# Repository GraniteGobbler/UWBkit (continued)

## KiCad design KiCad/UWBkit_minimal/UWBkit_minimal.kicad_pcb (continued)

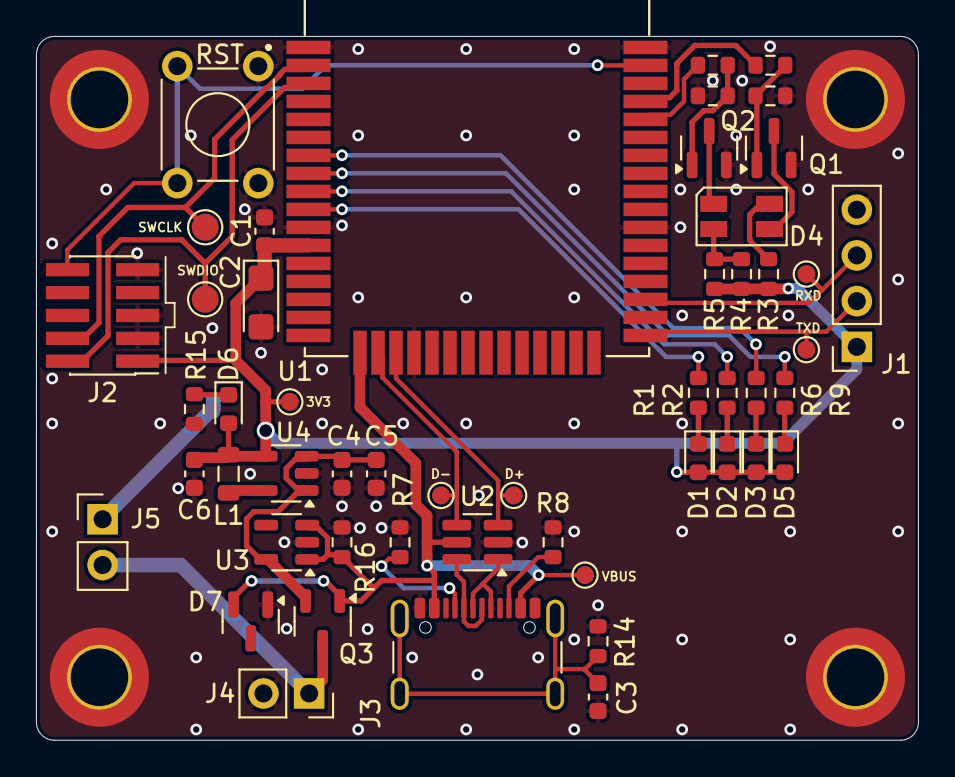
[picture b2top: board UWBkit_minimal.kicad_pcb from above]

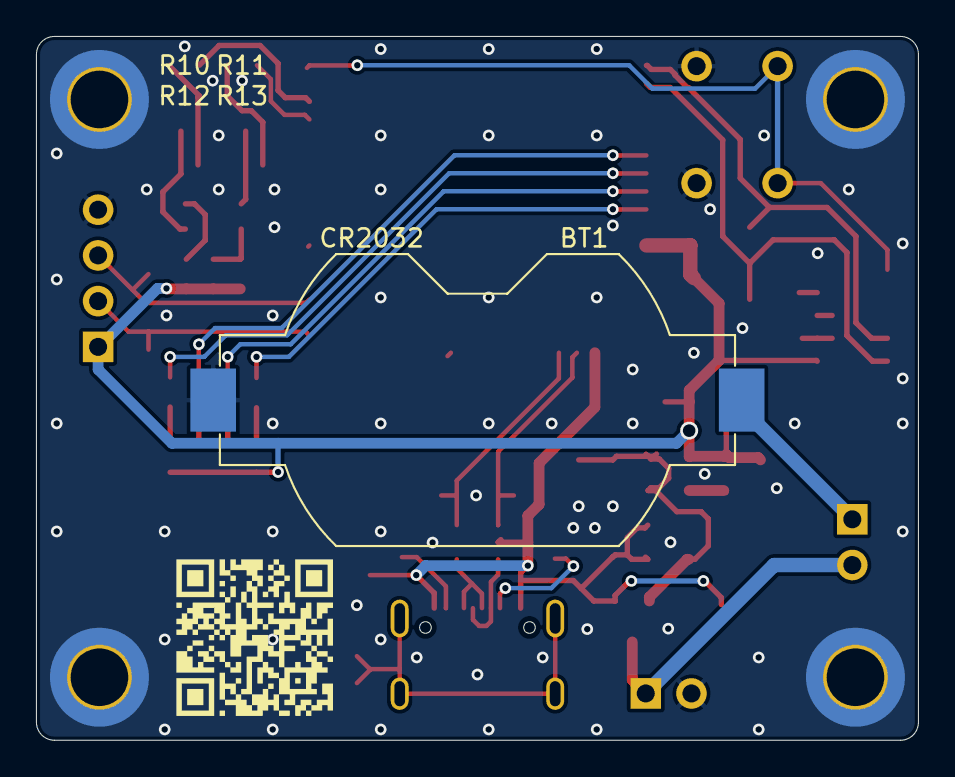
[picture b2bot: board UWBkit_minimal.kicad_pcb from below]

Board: 2 copper layers, 49.0 x 39.1 mm, 57 parts (2 on the bottom side), 36 nets.

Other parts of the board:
QR*****: Git_QR

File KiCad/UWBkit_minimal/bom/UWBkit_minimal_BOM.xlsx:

Reference | Qty | Value | Footprint |  | Mouser link
BT1 | 1 | CR2032 | Battery:BatteryHolder_Keystone_1058_1x2032 | https://cz.mouser.com/ProductDetail/Keystone-Electronics/105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 | https://cz.mouser.com/ProductDetail/Keystone-Electronics/105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
C1,C3,C4 | 3 | 100n | Capacitor_SMD:C_0603_1608Metric | https://cz.mouser.com/ProductDetail/YAGEO/CC0603JRX7R9BB104?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 | https://cz.mouser.com/ProductDetail/YAGEO/CC0603JRX7R9BB104?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
C2 | 1 | 10u | Capacitor_Tantalum_SMD:CP_EIA-3216-18_Kemet-A | https://cz.mouser.com/ProductDetail/KEMET/T491A106K010AT7280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 | https://cz.mouser.com/ProductDetail/KEMET/T491A106K010AT7280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
C5,C6 | 2 | 10u | Capacitor_SMD:C_0603_1608Metric | https://cz.mouser.com/ProductDetail/Murata-Electronics/GRM18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 | https://cz.mouser.com/ProductDetail/Murata-Electronics/GRM18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
D1 | 1 | G | LED_SMD:LED_0603_1608Metric | https://cz.mouser.com/ProductDetail/Wurth-Elektronik/150060G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 | https://cz.mouser.com/ProductDetail/Wurth-Elektronik/150060G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
D2 | 1 | B | LED_SMD:LED_0603_1608Metric | https://cz.mouser.com/ProductDetail/Wurth-Elektronik/150060B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 | https://cz.mouser.com/ProductDetail/Wurth-Elektronik/150060B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
D3,D5,D6 | 3 | R | LED_SMD:LED_0603_1608Metric | https://cz.mouser.com/ProductDetail/Wurth-Elektronik/150060R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 | https://cz.mouser.com/ProductDetail/Wurth-Elektronik/150060R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
D4 | 1 | LSG T676-P7R-1-0+N7P9-24 | LED_Dual:LED_Dual_OSRAM-PLCC4_3.2x2.8mm | https://cz.mouser.com/ProductDetail/ams-OSRAM/LSG-T676-P7R-1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 | https://cz.mouser.com/ProductDetail/ams-OSRAM/LSG-T676-P7R-1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
D7 | 1 | PESD5V2S2UT | Package_TO_SOT_SMD:SOT-23 | https://cz.mouser.com/ProductDetail/Nexperia/PESD5V2S2UT-QR?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 | https://cz.mouser.com/ProductDetail/Nexperia/PESD5V2S2UT-QR?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
J1 | 1 | Conn_UART | Connector_PinSocket_2.54mm:PinSocket_1x04_P2.54mm_Vertical | https://cz.mouser.com/ProductDetail/Samtec/SSQ-104-01-G-S?qs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 | https://cz.mouser.com/ProductDetail/Samtec/SSQ-104-01-G-S?qs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
J2 | 1 | Conn_SWD | Connector_PinHeader_1.27mm:PinHeader_2x05_P1.27mm_Vertical_SMD | https://cz.mouser.com/ProductDetail/Samtec/SHF-105-01-L-D-SM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 | https://cz.mouser.com/ProductDetail/Samtec/SHF-105-01-L-D-SM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
J3 | 1 | USB_C_Receptacle_USB2.0_14P | Connector_USB:USB_C_Receptacle_GCT_USB4105-xx-A_16P_TopMnt_Horizontal | https://cz.mouser.com/ProductDetail/GCT/USB4105-GF-A?qs=KUoI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 | https://cz.mouser.com/ProductDetail/GCT/USB4105-GF-A?qs=KUoI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
J4 | 1 | Conn_BATT | Connector_PinSocket_2.54mm:PinSocket_1x02_P2.54mm_Vertical | https://cz.mouser.com/ProductDetail/Amphenol-FCI/76308-102LF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 | https://cz.mouser.com/ProductDetail/Amphenol-FCI/76308-102LF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
J5 | 1 | Jumper_Cell_NO | Connector_PinHeader_2.54mm:PinHeader_1x02_P2.54mm_Vertical | https://cz.mouser.com/ProductDetail/Amphenol-FCI/10129378-91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 | https://cz.mouser.com/ProductDetail/Amphenol-FCI/10129378-91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
L1 | 1 | 2.2u | Inductor_SMD:L_0805_2012Metric | https://cz.mouser.com/ProductDetail/TDK/MLZ2012M2R2HT000?qs=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 | https://cz.mouser.com/ProductDetail/TDK/MLZ2012M2R2HT000?qs=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
Q1,Q2 | 2 | BSS138 | Package_TO_SOT_SMD:SOT-23 | https://cz.mouser.com/ProductDetail/onsemi-Fairchild/BSS138?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 | https://cz.mouser.com/ProductDetail/onsemi-Fairchild/BSS138?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
Q3 | 1 | BSS84 | Package_TO_SOT_SMD:SOT-23-3 | https://cz.mouser.com/ProductDetail/onsemi-Fairchild/BSS84?q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 | https://cz.mouser.com/ProductDetail/onsemi-Fairchild/BSS84?q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
R1 | 1 | 200R | Resistor_SMD:R_0603_1608Metric | https://cz.mouser.com/ProductDetail/YAGEO/RT0603DRD07200RL?q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 | https://cz.mouser.com/ProductDetail/YAGEO/RT0603DRD07200RL?q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
R2 | 1 | 30R | Resistor_SMD:R_0603_1608Metric | https://cz.mouser.com/ProductDetail/YAGEO/RT0603DRE0730RL?qs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 | https://cz.mouser.com/ProductDetail/YAGEO/RT0603DRE0730RL?qs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
R3 | 1 | 150R | Resistor_SMD:R_0603_1608Metric | https://cz.mouser.com/ProductDetail/YAGEO/AC0603FR-10150RL?q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 | https://cz.mouser.com/ProductDetail/YAGEO/AC0603FR-10150RL?q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
R4 | 1 | 330R | Resistor_SMD:R_0603_1608Metric | https://cz.mouser.com/ProductDetail/YAGEO/RE0603FRE07330RL?q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 | https://cz.mouser.com/ProductDetail/YAGEO/RE0603FRE07330RL?q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
R5 | 1 | 220R | Resistor_SMD:R_0603_1608Metric | https://cz.mouser.com/ProductDetail/Vishay/CRCW0603220RFKEC?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 | https://cz.mouser.com/ProductDetail/Vishay/CRCW0603220RFKEC?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
R6,R9,R15 | 3 | 300R | Resistor_SMD:R_0603_1608Metric | https://cz.mouser.com/ProductDetail/Panasonic/ERA-3AEB301V?q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 | https://cz.mouser.com/ProductDetail/Panasonic/ERA-3AEB301V?q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
R7,R8 | 2 | 5k1 | Resistor_SMD:R_0603_1608Metric | https://cz.mouser.com/ProductDetail/Vishay/CRCW06035K10FKEBC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 | https://cz.mouser.com/ProductDetail/Vishay/CRCW06035K10FKEBC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
R10,R11 | 2 | 1k | Resistor_SMD:R_0603_1608Metric | https://cz.mouser.com/ProductDetail/Vishay-Draloric/RCA06031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 | https://cz.mouser.com/ProductDetail/Vishay-Draloric/RCA06031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
R12,R13,R16 | 3 | 100k | Resistor_SMD:R_0603_1608Metric | https://cz.mouser.com/ProductDetail/YAGEO/RT0603BRD07100KL?q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 | https://cz.mouser.com/ProductDetail/YAGEO/RT0603BRD07100KL?q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
R14 | 1 | 10k | Resistor_SMD:R_0603_1608Metric | https://cz.mouser.com/ProductDetail/YAGEO/RC0603FR-7W10KL?qs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 | https://cz.mouser.com/ProductDetail/YAGEO/RC0603FR-7W10KL?qs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
SW1 | 1 | SW_Push | Button_Switch_THT:SW_TH_Tactile_Omron_B3F-106x | https://cz.mouser.com/ProductDetail/Omron-Electronics/B3F-10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 | https://cz.mouser.com/ProductDetail/Omron-Electronics/B3F-10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
U2 | 1 | IP4234CZ6 | Package_TO_SOT_SMD:SC-74-6_1.55x2.9mm_P0.95mm | https://cz.mouser.com/ProductDetail/Nexperia/IP4234CZ6125?qs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 | https://cz.mouser.com/ProductDetail/Nexperia/IP4234CZ6125?qs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
U3 | 1 | MAX40203AUK+T | Package_TO_SOT_SMD:SOT-23-5 | https://cz.mouser.com/ProductDetail/Analog-Devices-Maxim-Int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 | https://cz.mouser.com/ProductDetail/Analog-Devices-Maxim-Int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
U4 | 1 | XC9285B33CMR-G | Package_TO_SOT_SMD:SOT-23-5 | https://cz.mouser.com/ProductDetail/Torex-Semiconductor/XC92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 | https://cz.mouser.com/ProductDetail/Torex-Semiconductor/XC92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

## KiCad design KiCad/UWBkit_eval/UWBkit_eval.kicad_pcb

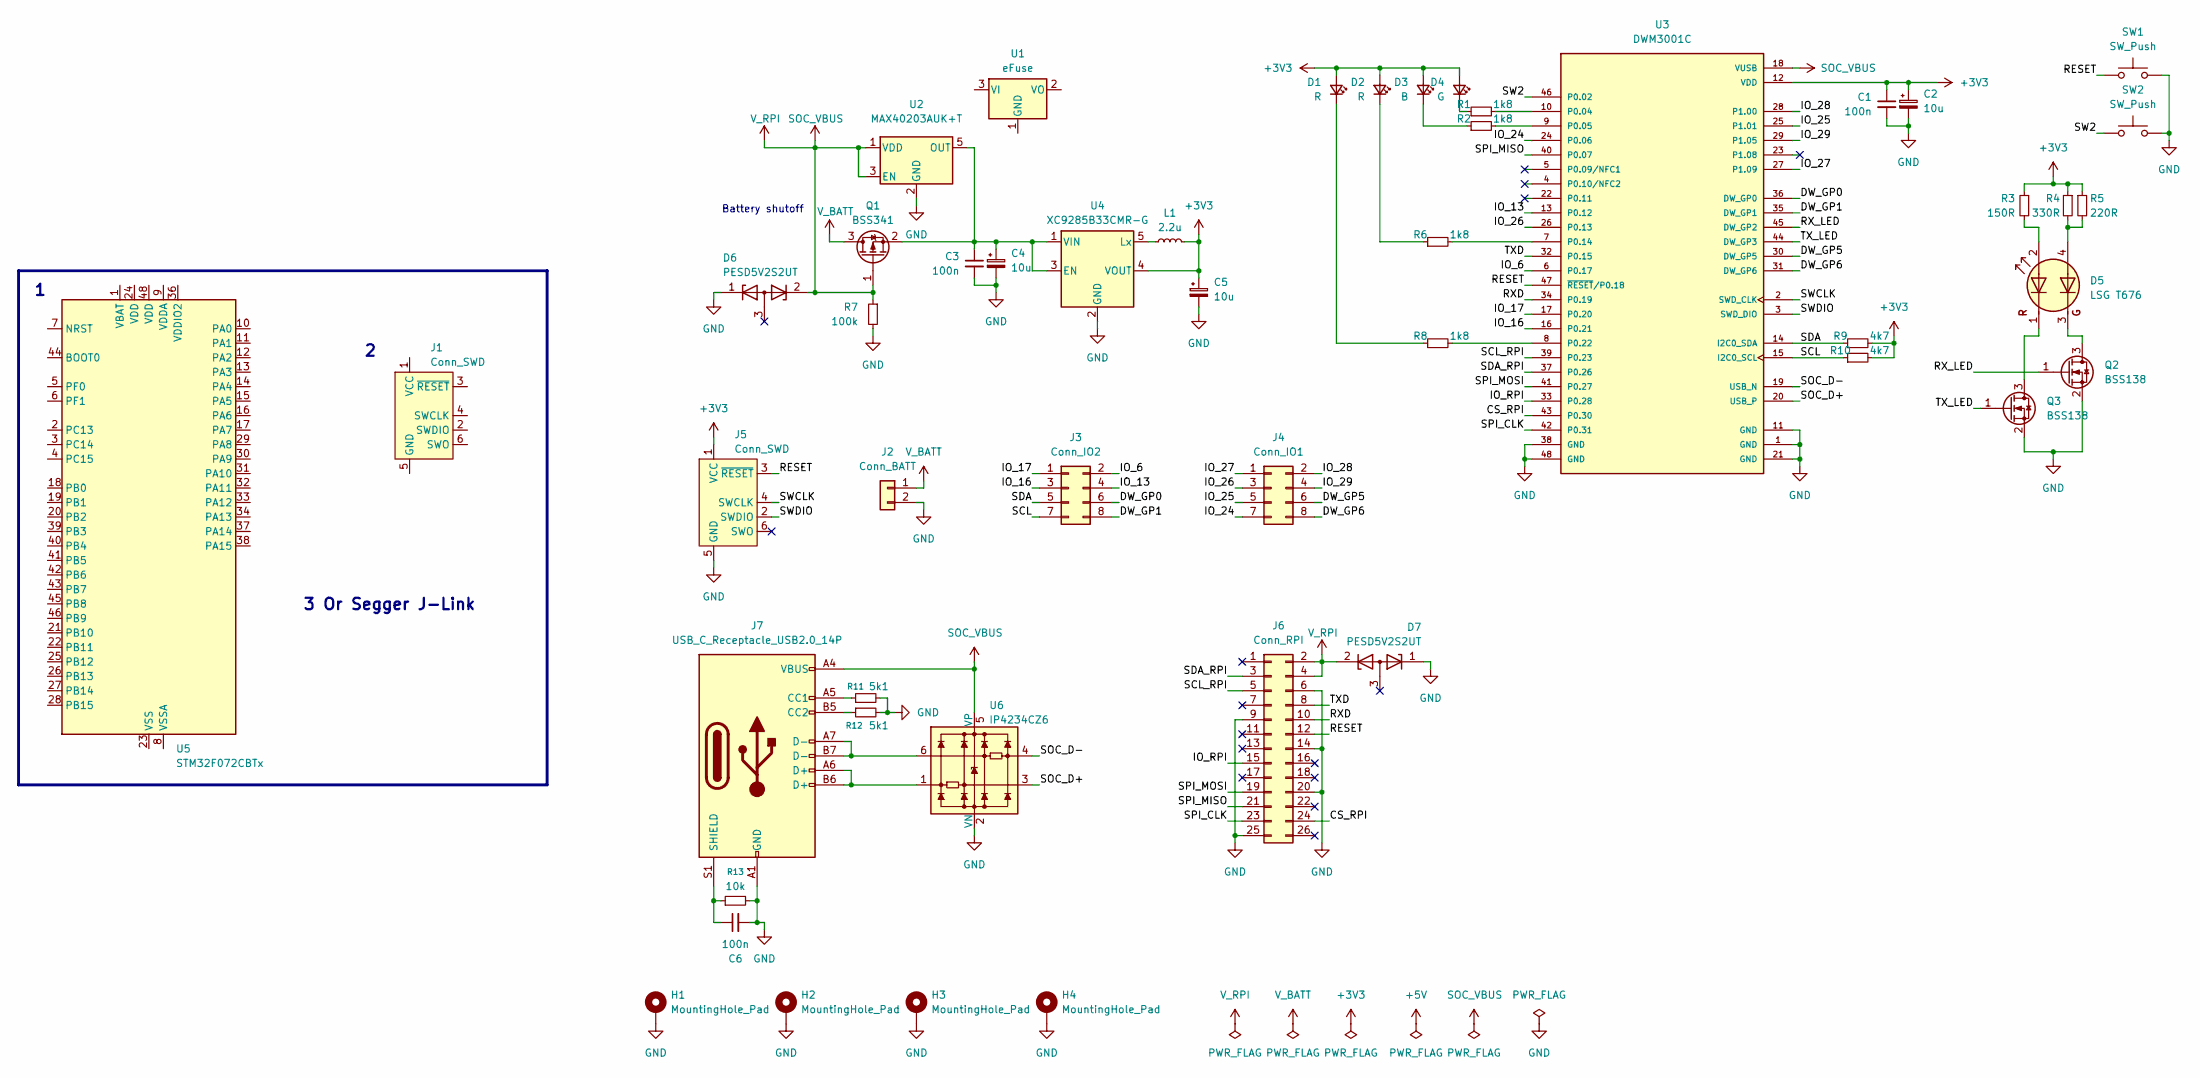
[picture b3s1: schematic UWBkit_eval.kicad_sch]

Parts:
C1, C3, C6: 100n; C_0603_1608Metric
C2, C4, C5: 10u; CP_EIA-3216-18_Kemet-A
D1, D2: R; LED_0603_1608Metric
D3: B; LED_0603_1608Metric
D4: G; LED_0603_1608Metric
D5: LSG T676; LED_Dual_OSRAM-PLCC4_3.2x2.8mm
D6, D7: PESD5V2S2UT; SOT-23
H1, H2, H3, H4: MountingHole_Pad; MountingHole_3.2mm_M3_ISO14580_Pad_TopBottom
J1, J5: Conn_SWD; Tag-Connect_TC2030-IDC-FP_2x03_P1.27mm_Vertical
J2: Conn_BATT; PinSocket_1x02_P2.54mm_Vertical
J3: Conn_IO2; PinHeader_2x04_P2.54mm_Vertical
J4: Conn_IO1; PinHeader_2x04_P2.54mm_Vertical
J6: Conn_RPI; PinSocket_2x13_P2.54mm_Vertical
J7: USB_C_Receptacle_USB2.0_14P; USB_C_Receptacle_GCT_USB4105-xx-A_16P_TopMnt_Horizontal
L1: 2.2u; L_0805_2012Metric
Q1: BSS341; SOT-23-3
Q2, Q3: BSS138; SOT-23
R1, R2, R6, R8: 1k8; R_0603_1608Metric
R3: 150R; R_0603_1608Metric
R4: 330R; R_0603_1608Metric
R5: 220R; R_0603_1608Metric
R7: 100k; R_0603_1608Metric
R9, R10: 4k7; R_0603_1608Metric
R11, R12: 5k1; R_0603_1608Metric
R13: 10k; R_0603_1608Metric
SW1, SW2: SW_Push; SW_TH_Tactile_Omron_B3F-106x
U1: eFuse; TSOT-23
U2: MAX40203AUK+T; SOT-23-5
U3: DWM3001C; PARTREV Rev C
U4: XC9285B33CMR-G; SOT-23-5
U5: STM32F072CBTx; LQFP-48_7x7mm_P0.5mm
U6: IP4234CZ6; SC-74-6_1.55x2.9mm_P0.95mm

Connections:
+3V3: C1.1, C2.1, C5.1, D1.2 (A), D2.2 (A), D3.2 (A), D4.2 (A), J5.1 (VCC), L1.2, R3.1, R4.1, R5.1, R9.2, R10.2, U3.12 (VDD), U4.4 (VOUT)
/CS_RPI: J6.24, U3.43 (P0.30)
/DW_GP0: J3.6, U3.36 (DW_GP0)
/DW_GP1: J3.8, U3.35 (DW_GP1)
/DW_GP5: J4.6, U3.30 (DW_GP5)
/DW_GP6: J4.8, U3.31 (DW_GP6)
/IO_6: J3.2, U3.6 (P0.17)
/IO_13: J3.4, U3.13 (P0.12)
/IO_16: J3.3, U3.16 (P0.21)
/IO_17: J3.1, U3.17 (P0.20)
/IO_24: J4.7, U3.24 (P0.06)
/IO_25: J4.5, U3.25 (P1.01)
/IO_26: J4.3, U3.26 (P0.13)
/IO_27: J4.1, U3.27 (P1.09)
/IO_28: J4.2, U3.28 (P1.00)
/IO_29: J4.4, U3.29 (P1.05)
/IO_RPI: J6.15, U3.33 (P0.28)
/RESET: J5.3 (~RESET), J6.12, SW1.2, U3.47 (~RESET/P0.18)
/RXD: J6.10, U3.34 (P0.19)
/RX_LED: Q2.1 (G), U3.45 (DW_GP2)
/SCL: J3.7, R10.1, U3.15 (I2C0_SCL)
/SCL_RPI: J6.5, U3.39 (P0.23)
/SDA: J3.5, R9.1, U3.14 (I2C0_SDA)
/SDA_RPI: J6.3, U3.37 (P0.26)
/SOC_D+: U3.20 (USB_P), U6.3
/SOC_D-: U3.19 (USB_N), U6.4
/SPI_CLK: J6.23, U3.42 (P0.31)
/SPI_MISO: J6.21, U3.40 (P0.07)
/SPI_MOSI: J6.19, U3.41 (P0.27)
/SW2: SW2.2, U3.46 (P0.02)
/SWCLK: J5.4 (SWCLK), U3.2 (SWD_CLK)
/SWDIO: J5.2 (SWDIO), U3.3 (SWD_DIO)
/TXD: J6.8, U3.32 (P0.15)
/TX_LED: Q3.1 (G), U3.44 (DW_GP3)
GND: C1.2, C2.2, C3.2, C4.2, C5.2, C6.2, D6.1 (K), D7.1 (K), H1.1, H2.1, H3.1, H4.1, J2.2, J5.5 (GND), J6.6, J6.9, J6.14, J6.20, J6.25, J7.A1 (GND), J7.A12 (GND), J7.B1 (GND), J7.B12 (GND), Q2.2 (S), Q3.2 (S), R7.2, R11.2, R12.2, R13.2, SW1.1, SW2.1, U2.2 (GND), U3.1 (GND), U3.11 (GND), U3.21 (GND), U3.38 (GND), U3.48 (GND), U4.2 (GND), U6.2 (VN)
unnamed: D1.1 (K), R8.1
unnamed: D2.1 (K), R6.1
unnamed: D3.1 (K), R2.1
unnamed: D4.1 (K), R1.1
unnamed: D5.2 (A1), R3.2
unnamed: D5.4 (A2), R4.2, R5.2
unnamed: D5.1 (K1), Q3.3 (D)
unnamed: D5.3 (K2), Q2.3 (D)
unnamed: J7.A5 (CC1), R11.1
unnamed: J7.B5 (CC2), R12.1
unnamed: J7.A6 (D+), J7.B6 (D+), U6.1
unnamed: J7.A7 (D-), J7.B7 (D-), U6.6
unnamed: C6.1, J7.S1 (SHIELD), R13.1
unnamed: C3.1, C4.1, Q1.2 (S), U2.5 (OUT), U4.1 (VIN), U4.3 (EN)
unnamed: R1.2, U3.10 (P0.04)
unnamed: R2.2, U3.9 (P0.05)
unnamed: R6.2, U3.7 (P0.14)
unnamed: R8.2, U3.8 (P0.22)
unnamed: L1.1, U4.5 (Lx)
unnamed: U5.23 (VSS), U5.35 (VSS), U5.47 (VSS)
SOC_VBUS: D6.2 (K), D7.2 (K), J6.2, J6.4, J7.A4 (VBUS), J7.A9 (VBUS), J7.B4 (VBUS), J7.B9 (VBUS), Q1.1 (G), R7.1, U2.1 (VDD), U2.3 (EN), U3.18 (VUSB), U6.5 (VP)
V_BATT: J2.1, Q1.3 (D)

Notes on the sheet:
3 Or Segger J-Link
Battery shutoff

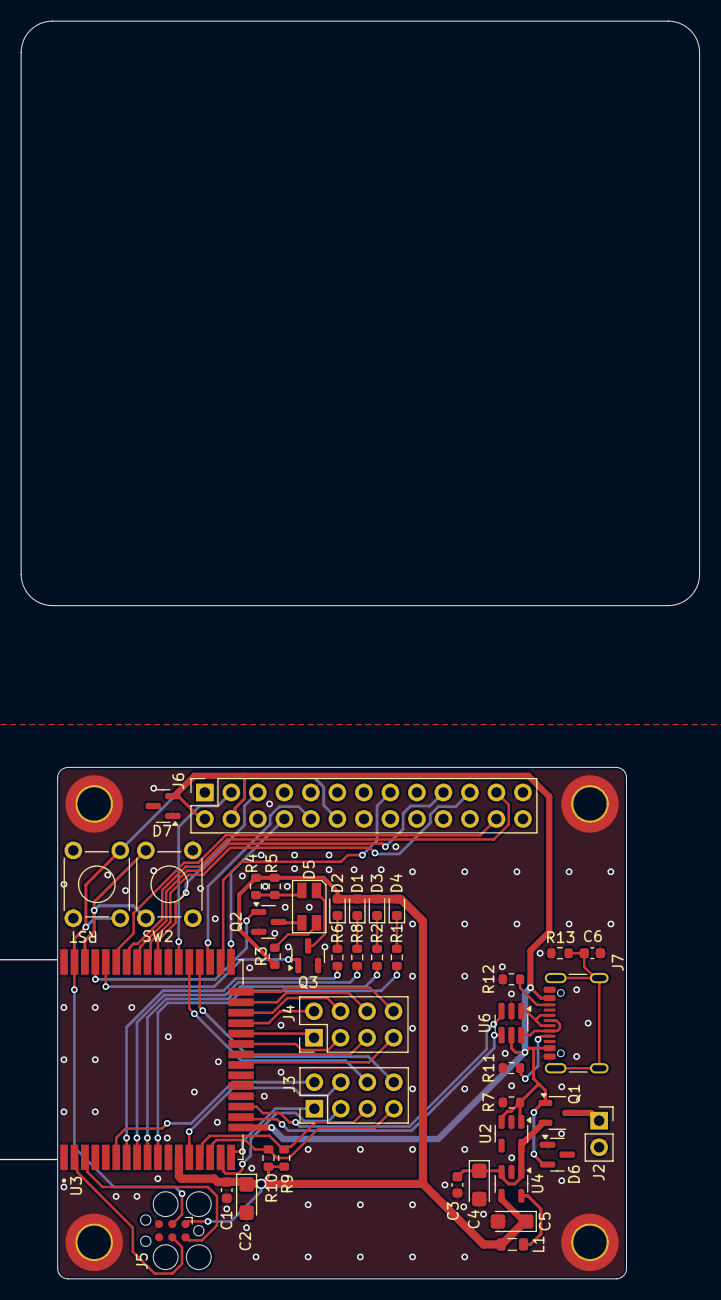
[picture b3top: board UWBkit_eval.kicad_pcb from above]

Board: 2 copper layers, 54.5 x 49.0 mm, 46 parts (0 on the bottom side), 56 nets.

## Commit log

2025-09-17 Updated to exclude some KiCad files
2025-09-17 Added RF module to schematic
2025-09-19 Added usb port
2025-09-19 Added connectors
2025-09-21 Assigned pins to connectors, added battery protection, edited LED footprint
2025-09-24 First version of the board
2025-09-29 Revised layout to be more compact
2025-09-30 Prepared PCB for RPI layout
2025-10-02 Added a new variant of the PCB
2025-10-02 Progress on minimal design
2025-10-02 Added power led, test points, modified layout
2025-10-03 Minor additions
2025-10-08 Minor changes, added a footprint with QR code
2025-10-15 Generated BOM
2025-10-15 Modified links
2025-11-12 Updated pinout for SWD connector
2025-11-25 Added mechanical models
2025-12-13 Fixed PCB .STEP export
2025-12-15 PDF export
2025-12-18 Remade the lid to accept an OLED display
2025-12-18 Updated parts and assembly
2026-01-01 Removed unused KiCad project
2026-01-01 Updated BOM link for SWD header
2026-01-01 Updated gitignore
2026-01-04 Added missing firmware files
2026-02-01 Added footprint for chip antenna
2026-02-05 Fixed a missing connection to JTAG
2026-02-05 Wired connections to SoC
2026-02-07 Added components to schematic
2026-02-08 First version of PCB
2026-02-10 Modified layout, uncovered RF traces
2026-02-15 Added reset pullup for CP2014
2026-02-15 United 5V rails, modified layout of connectors
2026-02-15 Added placeholder silkscreen elements
2026-02-15 Generated preliminary fab files
2026-02-18 Added connector description
2026-02-21 Removed UWA.01, added CTS/RTS connections
2026-02-22 Redone RF trace, repositioned UWC.20 and mounting holes
2026-02-22 Improved placement of ICs and ports and the board is now smaller
2026-02-22 Moved silkscreen text to be more visible
2026-02-23 Moved pi-filter past R8 shorting resistor
2026-02-23 Moved pi-filter
2026-02-24 Release V1.0
2026-02-28 Generated BOM for V1
2026-03-10 Fixed bottom silkscreen positioning for release V1.1
2026-03-26 Restructured files
2026-05-04 Added STL files for 3D print
2026-05-12 Added comments
2026-05-12 Edited dwt_config comments
2026-05-12 Removed unused code
2026-05-17 Added diagnostic data detection and parsing
2026-05-18 Added custom ZEP dissector
2026-05-24 Updated max acceptable length
2026-05-24 Renamed old dissector
2026-05-24 Rewritten reader for custom packets
